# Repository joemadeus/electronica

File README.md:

# led-module
A PCB for a four-LED (plus indicators) light

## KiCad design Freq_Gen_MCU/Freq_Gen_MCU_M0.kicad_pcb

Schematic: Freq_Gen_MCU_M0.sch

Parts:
ADJ_C0, ADJ_C1, ADJ_C2: 100n; C_0805_2012Metric_Pad1.15x1.40mm_HandSolder
ADJ_R0, ADJ_R1, ADJ_R2: 1k; R_0805_2012Metric_Pad1.15x1.40mm_HandSolder
ADJ_SW0, ADJ_SW1, ADJ_SW2: SW_Push; SW_CuK_EP11SD1A
BAT_C1, BAT_C2: 4.7u; C_0805_2012Metric_Pad1.15x1.40mm_HandSolder
BAT_LED1: Conn_01x02; PinHeader_1x02_P1.27mm_Vertical
BAT_R1: 5.1k; R_0805_2012Metric_Pad1.15x1.40mm_HandSolder
BAT_R2: 1k; R_0805_2012Metric_Pad1.15x1.40mm_HandSolder
BAT_U1: MCP73831-2-OT; SOT-23-5
CLK_C1, CLK_C2: 100n; C_0805_2012Metric_Pad1.15x1.40mm_HandSolder
CLK_U1: SI5351A; MSOP-10_3x3mm_P0.5mm
CLK_Y1: Crystal_GND24; Crystal_SMD_3225-4Pin_3.2x2.5mm_HandSoldering
CONN_BAT1: CONN_BAT; JST_PH_S2B-PH-K_1x02_P2.00mm_Horizontal
CONN_USB1: USB; USB_Micro-B_Wuerth_629105150521_CircularHoles
DEBUG_J1: Conn_02x05_Odd_Even; PinHeader_2x05_P1.27mm_Vertical
DEBUG_R1: 1k; R_0805_2012Metric_Pad1.15x1.40mm_HandSolder
HELLO_D1: LED; LED_0805_2012Metric_Pad1.15x1.40mm_HandSolder
HELLO_R1: 6.8; R_0805_2012Metric_Pad1.15x1.40mm_HandSolder
I2C_J1: Conn_01x04; PinHeader_1x04_P1.27mm_Vertical
I2C_R1, I2C_R2: 4.7k; R_0805_2012Metric_Pad1.15x1.40mm_HandSolder
LO_C1, LO_C4: 9.1p; C_0805_2012Metric_Pad1.15x1.40mm_HandSolder
LO_C2, LO_C3: 22p; C_0805_2012Metric_Pad1.15x1.40mm_HandSolder
LO_CONN1: LO; SMA_Jack_Horizontal
LO_L1, LO_L3: 47n; L_0805_2012Metric_Pad1.15x1.40mm_HandSolder
LO_L2: 56n; L_0805_2012Metric_Pad1.15x1.40mm_HandSolder
PWR_C1: 220u; CP_Radial_D6.3mm_P2.50mm
PWR_C2, PWR_C3: 1u; C_0805_2012Metric_Pad1.15x1.40mm_HandSolder
PWR_C4: 10u; C_0805_2012Metric_Pad1.15x1.40mm_HandSolder
PWR_C5: 100n; C_0805_2012Metric_Pad1.15x1.40mm_HandSolder
PWR_CONN1: Conn_01x02; PinHeader_1x02_P1.27mm_Vertical
PWR_D1: D_Schottky; D_SOD-123F
PWR_LED1: Conn_01x02; PinHeader_1x02_P1.27mm_Vertical
PWR_Q1: DMG2301L; SOT-23_Handsoldering
PWR_R1: 10k; R_0805_2012Metric_Pad1.15x1.40mm_HandSolder
PWR_R2: 1k; R_0805_2012Metric_Pad1.15x1.40mm_HandSolder
PWR_U1: AP2112K-3.3; SOT-23-5
PWR_U2: TPD3E001DRLR; SOT-553
U1: ATSAML21E15B-AUT; TQFP-32_7x7mm_P0.8mm
VDDANA_C1: 100n; C_0805_2012Metric_Pad1.15x1.40mm_HandSolder
VDDCORE_C1: 1u; C_0805_2012Metric_Pad1.15x1.40mm_HandSolder
VDDCORE_C2: 100n; C_0805_2012Metric_Pad1.15x1.40mm_HandSolder
VDDIN_C1: 100n; C_0805_2012Metric_Pad1.15x1.40mm_HandSolder

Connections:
/ADJ_0: ADJ_C0.1, ADJ_R0.1, U1.5
/ADJ_1: ADJ_C1.1, ADJ_R1.1, U1.6
/ADJ_2: ADJ_C2.1, ADJ_R2.1, U1.7
/CLK: CLK_U1.10, LO_C1.1, LO_L1.1
/D+: CONN_USB1.3, PWR_U2.2, U1.24
/D-: CONN_USB1.2, PWR_U2.1, U1.23
/GPIO1: DEBUG_J1.6, U1.4
/HELLO: HELLO_R1.2, U1.25
/RESET: DEBUG_J1.10, U1.26
/SCL: CLK_U1.4, I2C_J1.4, I2C_R2.2, U1.18
/SDA: CLK_U1.5, I2C_J1.3, I2C_R1.2, U1.17
/SWCLK: DEBUG_J1.4, DEBUG_R1.2, U1.31
/SWIO: DEBUG_J1.2, U1.32
/VBAT: BAT_C2.1, BAT_U1.3, CONN_BAT1.2, PWR_Q1.3
/VBUS: BAT_C1.1, BAT_LED1.1, BAT_U1.4, PWR_D1.1 (K), PWR_Q1.1
/VDD: CLK_C1.1, CLK_C2.1, CLK_U1.1, CLK_U1.7, DEBUG_J1.1, DEBUG_R1.1, I2C_J1.2, I2C_R1.1, I2C_R2.1, PWR_C3.1, PWR_C4.1, PWR_LED1.1, PWR_U1.5, U1.9, U1.30, VDDANA_C1.1, VDDIN_C1.2
GND: ADJ_C0.2, ADJ_C1.2, ADJ_C2.2, ADJ_SW0.1, ADJ_SW1.1, ADJ_SW2.1, BAT_C1.2, BAT_C2.2, BAT_R1.2, BAT_U1.2, CLK_C1.2, CLK_C2.2, CLK_U1.8, CLK_Y1.2, CLK_Y1.4, CONN_BAT1.1, CONN_USB1.5, DEBUG_J1.3, DEBUG_J1.5, HELLO_D1.1 (K), I2C_J1.1, LO_C1.2, LO_C2.2, LO_C3.2, LO_C4.2, LO_CONN1.2, PWR_C1.2, PWR_C2.2, PWR_C3.2, PWR_C4.2, PWR_C5.2, PWR_R2.2, PWR_U1.2, PWR_U2.3, U1.10, U1.28, VDDANA_C1.2, VDDCORE_C1.1, VDDCORE_C2.1, VDDIN_C1.1
unnamed: ADJ_R0.2, ADJ_SW0.2
unnamed: ADJ_R1.2, ADJ_SW1.2
unnamed: ADJ_R2.2, ADJ_SW2.2
unnamed: BAT_LED1.2, BAT_R2.1
unnamed: BAT_R1.1, BAT_U1.5
unnamed: BAT_R2.2, BAT_U1.1
unnamed: CLK_U1.2, CLK_Y1.1
unnamed: CLK_U1.3, CLK_Y1.3
unnamed: CONN_USB1.1, PWR_C5.1, PWR_D1.2 (A), PWR_U2.5
unnamed: HELLO_D1.2 (A), HELLO_R1.1
unnamed: LO_C2.1, LO_L1.2, LO_L2.1
unnamed: LO_C3.1, LO_L2.2, LO_L3.1
unnamed: LO_C4.1, LO_CONN1.1, LO_L3.2
unnamed: PWR_C1.1, PWR_C2.1, PWR_CONN1.2, PWR_R1.2, PWR_U1.1
unnamed: PWR_CONN1.1, PWR_Q1.2
unnamed: PWR_LED1.2, PWR_R2.1
unnamed: PWR_R1.1, PWR_U1.3
unnamed: U1.27, VDDCORE_C1.2, VDDCORE_C2.2

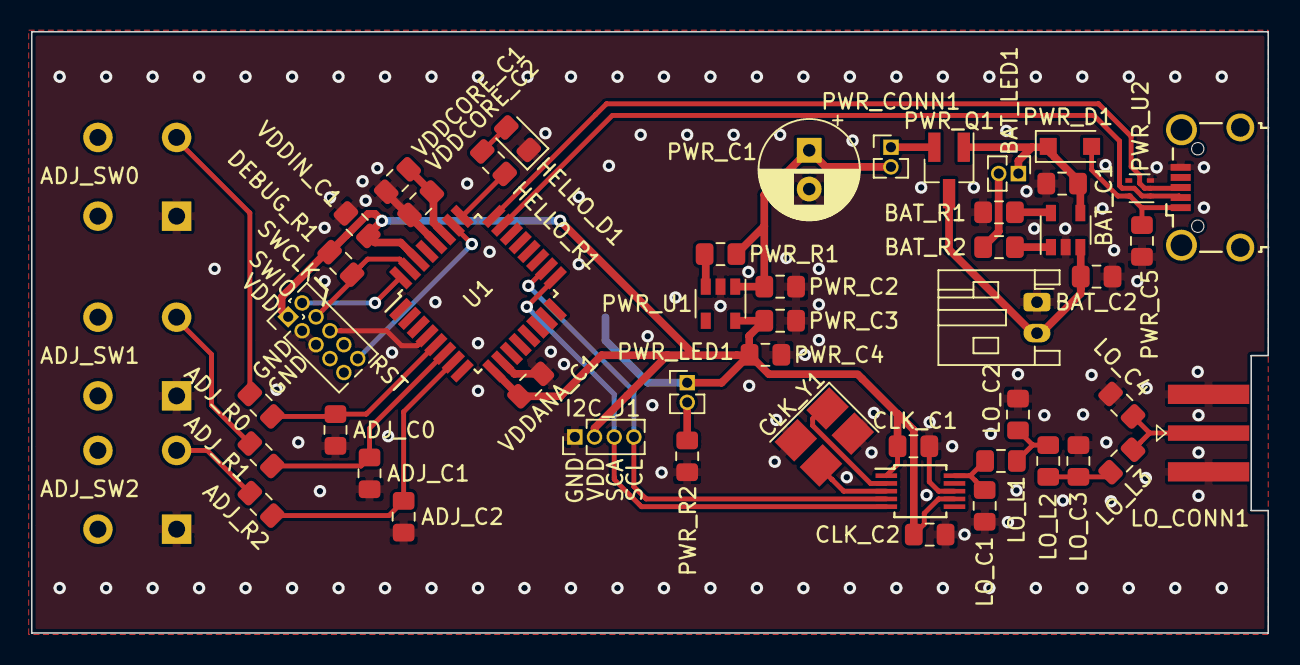
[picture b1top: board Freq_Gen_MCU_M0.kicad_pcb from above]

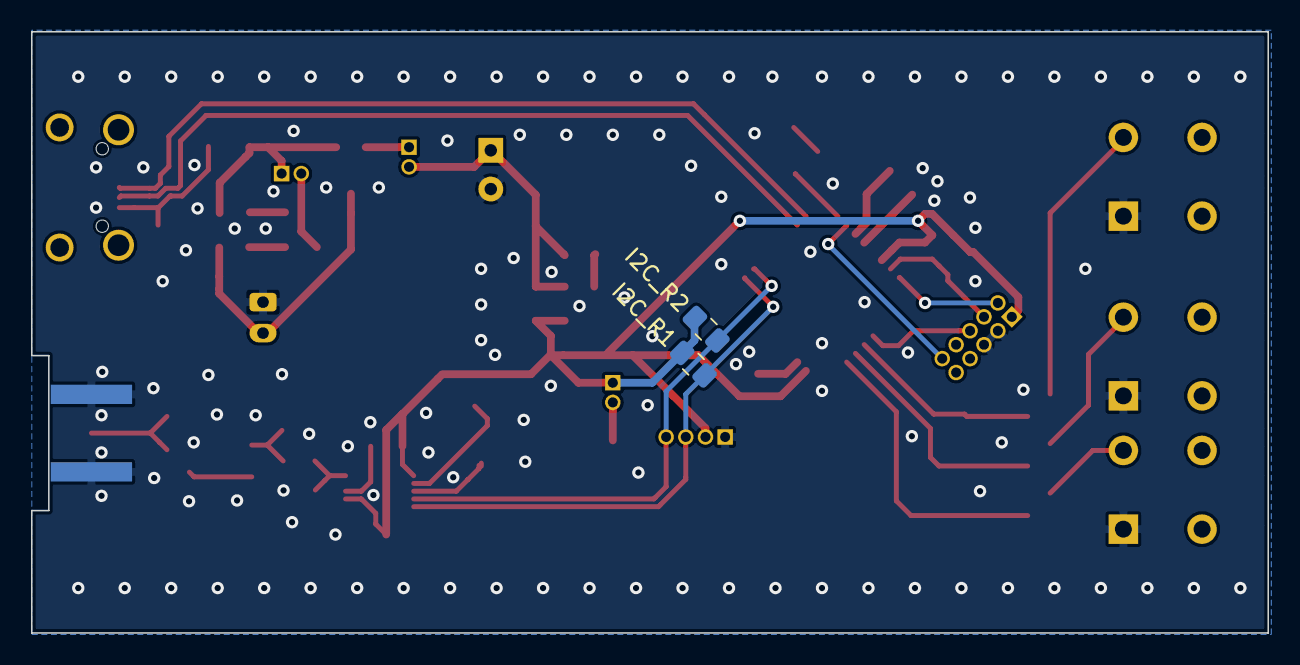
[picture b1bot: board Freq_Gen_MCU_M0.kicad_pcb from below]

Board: 2 copper layers, 79.8 x 38.8 mm, 54 parts (2 on the bottom side), 35 nets.

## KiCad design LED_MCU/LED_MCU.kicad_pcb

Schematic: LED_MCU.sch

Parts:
BAT_C1, BAT_C2: 4.7u; C_0805_2012Metric
BAT_C3: 0.1u; C_0805_2012Metric
BAT_R1: 5k; R_0805_2012Metric
BAT_R2: 1k; R_0805_2012Metric
BAT_U1: LTC2942-1; DFN-6-1EP_3x2mm_P0.5mm_EP1.65x1.35mm
BAT_U2: MCP73831-2-OT; SOT-23-5
C1, C3, C4: 100n; C_0805_2012Metric
C2: 1u; C_0805_2012Metric
CONN_BAT1: CONN_BAT; JST_PH_S2B-PH-K_1x02_P2.00mm_Horizontal
CONN_USB1: USB; USB_Micro-B_Wuerth_629105150521_CircularHoles
H1, H3: MountingHole; MountingHole_2.5mm
H2, H4: MountingHole_Pad; MountingHole_2.7mm_M2.5_DIN965_Pad
HELLO_LED1: HELLO; D_0805_2012Metric_Castellated
HELLO_R1: 6.8; R_1206_3216Metric
IN_C1, IN_C2, IN_C3: 100n; C_0805_2012Metric
IN_J1: Conn_02x03_Odd_Even; PinSocket_2x03_P1.27mm_Vertical
IN_R1, IN_R2, IN_R3: 1k; R_0805_2012Metric
J1: Conn_02x05_Odd_Even; PinHeader_2x05_P1.27mm_Vertical
J2: Conn_02x06_Row_Letter_Last; PinHeader_2x06_P1.27mm_Vertical
J_I2C1: Conn_01x04; PinHeader_1x04_P1.27mm_Vertical
J_RESET1: Conn_01x02; PinHeader_1x02_P1.27mm_Vertical
LED_B1: LED_B; LED_D3.0mm
LED_G1: LED_G; LED_D3.0mm
LED_O1: LED_O; LED_0805_2012Metric_Castellated
LED_R1: LED_R; LED_D3.0mm
LED_W1, LED_W2, LED_W3: LED_W; D_1206_3216Metric_Pad1.42x1.75mm_HandSolder
PWR_C1: 100n; C_0805_2012Metric
PWR_C2: 330uF; CP_Radial_D6.3mm_P2.50mm
PWR_C3, PWR_C5, PWR_C7: 1u; C_0805_2012Metric
PWR_C4: 4.7u; C_0805_2012Metric
PWR_C6: 10u; C_0805_2012Metric
PWR_CONN1: Conn_01x02; PinHeader_1x02_P1.27mm_Vertical
PWR_D1: D_Schottky; D_SOD-123F
PWR_Q1: DMG2301L; SOT-23
PWR_R1: 10k; R_0805_2012Metric
PWR_U1: TPD3E001DRLR; SOT-553
PWR_U2: AP2112K-3.3; SOT-23-5
PWR_U3: LD1117S33TR_SOT223; SOT-223-3_TabPin2
Q1, Q2, Q3: Q_DUAL_NMOS; SO-8_3.9x4.9mm_P1.27mm
R1: 1k; R_0805_2012Metric
R2, R3: 4.7k; R_0805_2012Metric
RB1: 470; R_1206_3216Metric
RB2: 6.8; R_1206_3216Metric
RG1: 470; R_1206_3216Metric
RG2: 10; R_1206_3216Metric
RR1: 470; R_1206_3216Metric
RR2: 10; R_1206_3216Metric
RW1, RW2, RW3: 470; R_1206_3216Metric
RW1-1, RW1-2, RW1-3, RW2-1, RW2-2, RW2-3, RW3-1, RW3-2, RW3-3: 6.8; R_1206_3216Metric
U1: ATSAML21E16B-AUT; TQFP-32_7x7mm_P0.8mm

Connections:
/D+: CONN_USB1.3, PWR_U1.2, U1.24
/D-: CONN_USB1.2, PWR_U1.1, U1.23
/HELLO: HELLO_R1.1, U1.21
/IN1: IN_C1.1, IN_R1.2, U1.11
/IN2: IN_C2.1, IN_R2.2, U1.12
/IN3: IN_C3.1, IN_R3.2, U1.13
/LED_B: RB1.2, U1.3
/LED_G: RG1.2, U1.5
/LED_R: RR1.2, U1.7
/LED_W1: RW1.2, U1.8
/LED_W2: RW2.2, U1.6
/LED_W3: RW3.2, U1.4
/PWR_CC: BAT_U1.5, U1.22
/RESET: J1.10, J_RESET1.1, U1.26
/SCL: BAT_U1.3, J_I2C1.2, R3.2, U1.18
/SDA: BAT_U1.4, J_I2C1.1, R2.2, U1.17
/SWCLK: J1.4, R1.2, U1.31
/SWIO: J1.2, U1.32
/VBAT: BAT_C2.1, BAT_C3.1, BAT_U1.1, BAT_U2.3, PWR_Q1.3
/VBUS: BAT_C1.1, BAT_U2.4, LED_O1.2 (A), PWR_D1.1 (K), PWR_Q1.1
/VCC: PWR_C2.1, PWR_C3.1, PWR_C7.1, PWR_CONN1.1, PWR_R1.2, PWR_U2.1, PWR_U3.3
/VDD: C1.1, C4.2, J1.1, J_I2C1.3, PWR_C5.1, PWR_C6.1, PWR_U2.5, R1.1, R2.1, R3.1, U1.9, U1.30
/V_LED: PWR_C4.1, PWR_U3.2, RB2.1, RG2.1, RR2.1, RW1-1.1, RW1-2.1, RW1-3.1, RW2-1.1, RW2-2.1, RW2-3.1, RW3-1.1, RW3-2.1, RW3-3.1
GND: BAT_C1.2, BAT_C2.2, BAT_C3.2, BAT_R1.2, BAT_U1.2, BAT_U2.2, C1.2, C2.1, C3.1, C4.1, CONN_BAT1.2, CONN_USB1.5, HELLO_LED1.1 (K), IN_C1.2, IN_C2.2, IN_C3.2, IN_J1.2, IN_J1.4, IN_J1.6, J1.3, J1.5, J_I2C1.4, J_RESET1.2, PWR_C1.2, PWR_C2.2, PWR_C3.2, PWR_C4.2, PWR_C5.2, PWR_C6.2, PWR_C7.2, PWR_U1.3, PWR_U2.2, PWR_U3.1, Q1.2, Q1.5, Q2.2, Q2.5, Q3.2, Q3.5, U1.10, U1.28
unnamed: BAT_R1.1, BAT_U2.5
unnamed: BAT_R2.1, LED_O1.1 (K)
unnamed: BAT_R2.2, BAT_U2.1
unnamed: BAT_U1.6, CONN_BAT1.1
unnamed: C2.2, C3.2, U1.27
unnamed: CONN_USB1.1, PWR_C1.1, PWR_D1.2 (A), PWR_U1.5
unnamed: HELLO_LED1.2 (A), HELLO_R1.2
unnamed: IN_J1.1, IN_R1.1
unnamed: IN_J1.3, IN_R2.1
unnamed: IN_J1.5, IN_R3.1
unnamed: J2.1, J2.3, J2.5, Q2.6
unnamed: J2.2, RW2-1.2
unnamed: J2.4, RW2-2.2
unnamed: J2.6, RW2-3.2
unnamed: J2.8, RW3-1.2
unnamed: J2.10, RW3-2.2
unnamed: J2.7, J2.9, J2.11, Q3.6
unnamed: J2.12, RW3-3.2
unnamed: LED_B1.1 (K), Q3.4
unnamed: LED_B1.2 (A), RB2.2
unnamed: LED_G1.1 (K), Q2.4
unnamed: LED_G1.2 (A), RG2.2
unnamed: LED_R1.1 (K), Q1.4
unnamed: LED_R1.2 (A), RR2.2
unnamed: LED_W1.1 (K), LED_W2.1 (K), LED_W3.1 (K), Q1.6
unnamed: LED_W1.2 (A), RW1-1.2
unnamed: LED_W2.2 (A), RW1-2.2
unnamed: LED_W3.2 (A), RW1-3.2
unnamed: PWR_CONN1.2, PWR_Q1.2
unnamed: PWR_R1.1, PWR_U2.3
unnamed: Q1.1, RW1.1
unnamed: Q1.3, RR1.1
unnamed: Q2.1, RW2.1
unnamed: Q2.3, RG1.1
unnamed: Q3.1, RW3.1
unnamed: Q3.3, RB1.1

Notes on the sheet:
RGB
WHITE
BATT CHARGING
BATT MONITORING
90mS 3V3 holdup @1A
USB PWR
BATT SWITCH
μP POWER
LED POWER

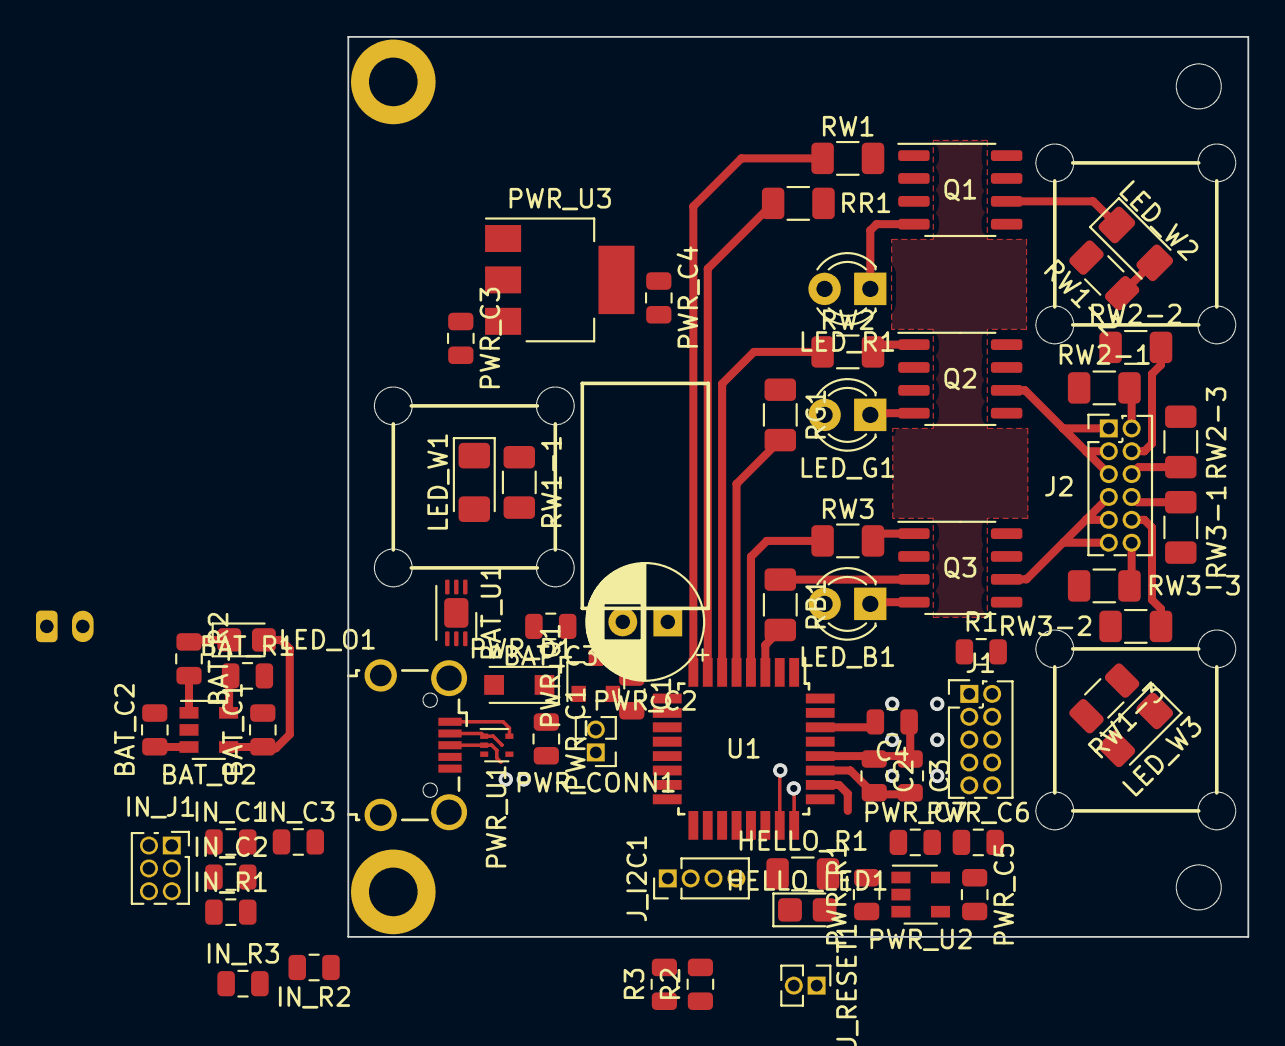
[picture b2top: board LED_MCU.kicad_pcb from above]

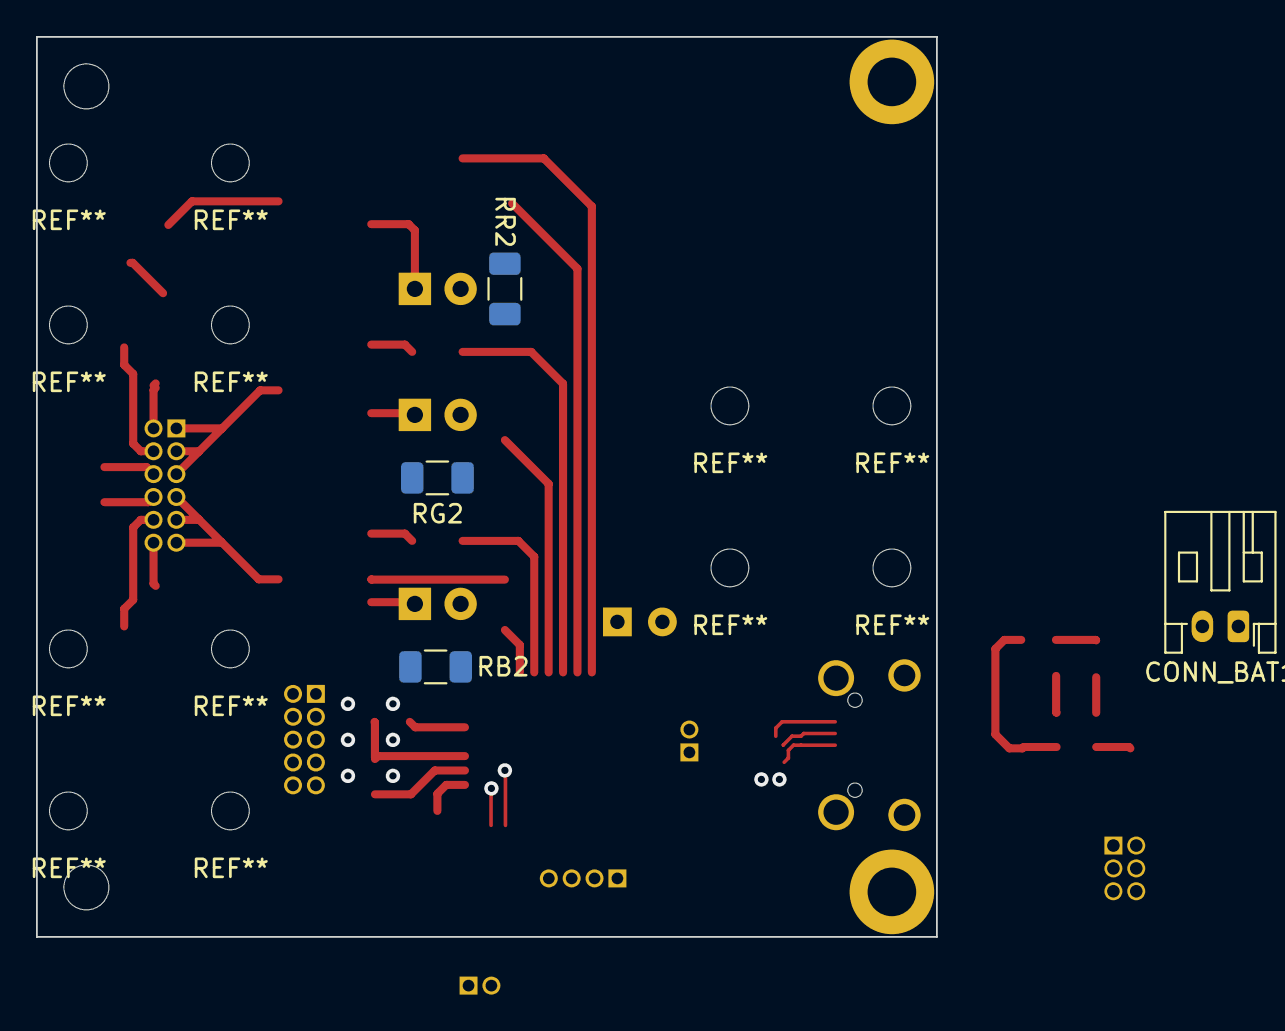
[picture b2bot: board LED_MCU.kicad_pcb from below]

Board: 2 copper layers, 50.0 x 50.0 mm, 76 parts (4 on the bottom side), 60 nets.

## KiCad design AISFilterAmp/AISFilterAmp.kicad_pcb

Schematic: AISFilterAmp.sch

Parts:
J_IN1: Conn_Coaxial; SMA_Jack_Horizontal
J_OUT1: Conn_Coaxial; SMA_Jack_Horizontal
PWR_C1: 4.7u; C_0805_2012Metric_Pad1.15x1.40mm_HandSolder
PWR_C2: 330p; C_0805_2012Metric_Pad1.15x1.40mm_HandSolder
PWR_C3: 10u; C_0805_2012Metric_Pad1.15x1.40mm_HandSolder
PWR_D1: D_Schottky; D_SOD-123F
PWR_J1: Conn_01x02_Female; PinHeader_1x02_P2.54mm_Vertical
PWR_L1: L; L_Taiyo-Yuden_NR-40xx_HandSoldering
PWR_L2: L; L_0805_2012Metric_Pad1.15x1.40mm_HandSolder
PWR_R1: 82.5k; R_0805_2012Metric_Pad1.15x1.40mm_HandSolder
PWR_R2: 13.3k; R_0805_2012Metric_Pad1.15x1.40mm_HandSolder
PWR_R3: 51.1k; R_0805_2012Metric_Pad1.15x1.40mm_HandSolder
RF_C1, RF_C3, RF_C5: 85.53p; C_0805_2012Metric_Pad1.15x1.40mm_HandSolder
RF_C2, RF_C4: 1.744p; C_0805_2012Metric_Pad1.15x1.40mm_HandSolder
RF_C6, RF_C7: C; C_0805_2012Metric_Pad1.15x1.40mm_HandSolder
RF_L1, RF_L3, RF_L5: 11.41n; L_0805_2012Metric_Pad1.15x1.40mm_HandSolder
RF_L2, RF_L4: 559.8n; L_0805_2012Metric_Pad1.15x1.40mm_HandSolder
U1: MSA0505; HP_MSA0505-4_HandSoldering
U2: LM2731XMF; SOT-23-5

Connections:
GND: J_IN1.2, J_OUT1.2, PWR_C1.2, PWR_C3.2, PWR_J1.1, PWR_R2.2, RF_C1.1, RF_C3.1, RF_C5.1, RF_L1.2, RF_L3.2, RF_L5.2, U1.2, U1.4, U2.2
unnamed: J_IN1.1, RF_C1.2, RF_L1.1, RF_L2.1
unnamed: J_OUT1.1, RF_C7.1
unnamed: PWR_C1.1, PWR_J1.2, PWR_L1.1, PWR_R3.2, U2.5
unnamed: PWR_C2.1, PWR_C3.1, PWR_D1.1 (K), PWR_L2.1, PWR_R1.1
unnamed: PWR_C2.2, PWR_R1.2, PWR_R2.1, U2.3
unnamed: PWR_D1.2 (A), PWR_L1.2, U2.1
unnamed: PWR_L2.2, RF_C7.2, U1.3
unnamed: PWR_R3.1, U2.4
unnamed: RF_C2.1, RF_C3.2, RF_L3.1, RF_L4.1
unnamed: RF_C2.2, RF_L2.2
unnamed: RF_C4.1, RF_C5.2, RF_C6.2, RF_L5.1
unnamed: RF_C4.2, RF_L4.2
unnamed: RF_C6.1, U1.1

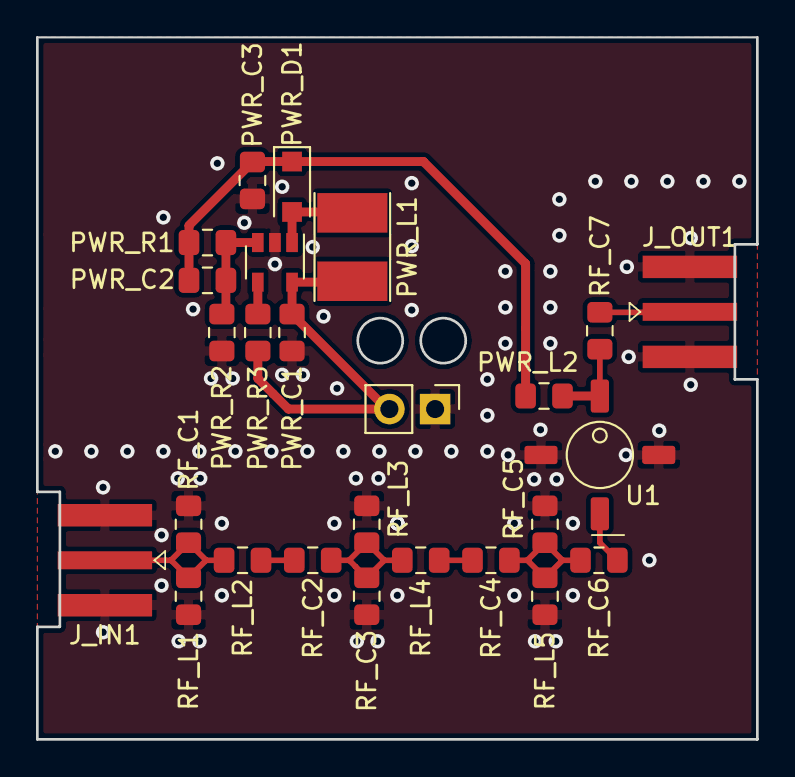
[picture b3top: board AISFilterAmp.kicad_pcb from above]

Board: 2 copper layers, 40.0 x 39.0 mm, 26 parts (0 on the bottom side), 14 nets.

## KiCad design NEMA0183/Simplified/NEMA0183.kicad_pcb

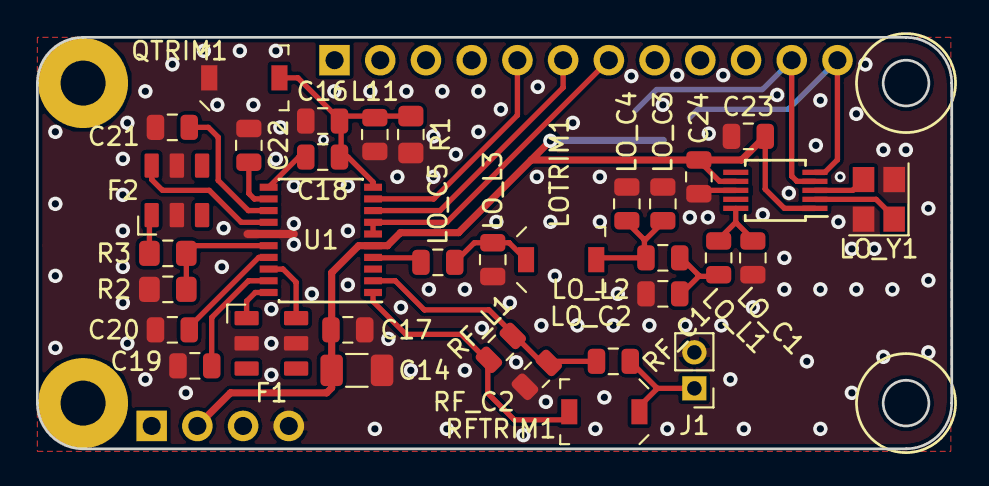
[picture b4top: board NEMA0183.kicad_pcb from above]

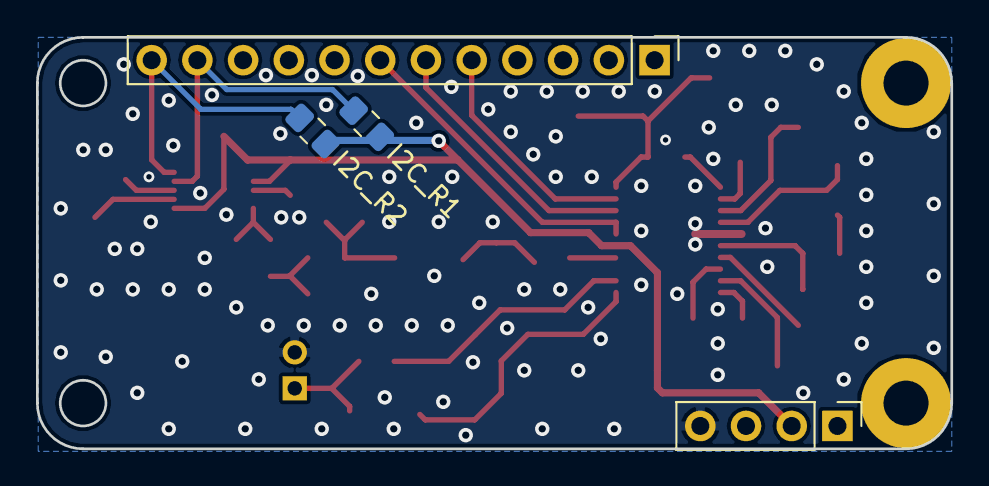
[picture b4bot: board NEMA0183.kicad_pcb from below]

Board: 2 copper layers, 50.8 x 22.9 mm, 38 parts (4 on the bottom side), 28 nets.

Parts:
C14: 22u; C_1206_3216Metric
C16: 30p; C_0805_2012Metric
C17, C23, C24: 100n; C_0805_2012Metric
C18: 4.7p; C_0805_2012Metric
C19, C20, C21, C22: 10n; C_0805_2012Metric
F1, F2: SFECF_10M7; Murata_SFECF-6_HandSoldering
I2C_R1, I2C_R2: 4.7k; R_0805_2012Metric_Pad1.15x1.40mm_HandSolder
J1: RF_IN; PinHeader_1x02_P2.00mm_Vertical
J2: Feather_Top_Female; PinHeader_Adafruit_Feather_Top
J3: Feather_Bottom_Female; PinHeader_1x04_P2.54mm_Vertical
L11: 5.6u; L_0805_2012Metric
LOTRIM1: JZ300; C_Trimmer_Voltronics_JZ
LO_C1, LO_C3: 9.1p; C_0805_2012Metric
LO_C2: 22p; C_0805_2012Metric
LO_C4: 100n; C_0805_2012Metric
LO_C5: 330p; C_0805_2012Metric
LO_L1, LO_L2: 47n; L_0805_2012Metric
LO_L3: 68n; L_0805_2012Metric
LO_U1: SI5351A; MSOP-10_3x3mm_P0.5mm
LO_Y1: Crystal_GND24; Crystal_SMD_3225-4Pin_3.2x2.5mm
QTRIM1: JZ100; C_Trimmer_Voltronics_JZ
R1: 10k; R_0805_2012Metric_Pad1.15x1.40mm_HandSolder
R2, R3: 0; R_0805_2012Metric_Pad1.15x1.40mm_HandSolder
RFTRIM1: JZ300; C_Trimmer_Voltronics_JZ
RF_C1: 82n; C_0805_2012Metric
RF_C2: 330p; C_0805_2012Metric
RF_L1: 68n; L_0805_2012Metric
U1: SA636DK; SSOP-20_4.4x6.5mm_P0.65mm

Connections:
/3V3: C14.1, C17.1, C23.1, C24.2, I2C_R1.1, I2C_R2.2, J3.2, LO_U1.1, LO_U1.7, U1.5
/DAT_OUT: J2.15, U1.9
/LO_IN: LO_C1.1, LO_L1.1, LO_U1.10
/POW_CON_IN: J2.07, U1.8
/RSSI_OUT: J2.11, U1.6, U1.7
/SCL: I2C_R1.2, J2.SCL, LO_U1.4
/SDA: I2C_R2.1, J2.SDA, LO_U1.5
GND: C14.2, C16.2, C17.2, C19.1, C20.1, C21.1, C22.1, C23.2, C24.1, F1.2, F1.5, F2.2, F2.5, J1.2, J3.4, L11.2, LO_C1.2, LO_C2.2, LO_C3.2, LO_C4.2, LO_L3.2, LO_U1.8, LO_Y1.2, LO_Y1.4, QTRIM1.1, R1.2, R2.2, RF_C2.2, U1.15
unnamed: C16.1, C18.2, L11.1, QTRIM1.2, R1.1, U1.10
unnamed: C18.1, U1.11
unnamed: C19.2, U1.19
unnamed: C20.2, U1.17
unnamed: C21.2, U1.13
unnamed: C22.2, U1.12
unnamed: F1.1, U1.20
unnamed: F1.6, U1.18
unnamed: F2.1, R3.2
unnamed: F2.6, U1.14
unnamed: J1.1, RFTRIM1.1, RF_C1.1
unnamed: LOTRIM1.1, LO_C5.1, LO_L3.1
unnamed: LOTRIM1.2, LO_C3.1, LO_C4.1, LO_L2.2
unnamed: LO_C2.1, LO_L1.2, LO_L2.1
unnamed: LO_C5.2, U1.4
unnamed: LO_U1.2, LO_Y1.1
unnamed: LO_U1.3, LO_Y1.3
unnamed: R2.1, R3.1, U1.16
unnamed: RFTRIM1.2, RF_L1.1, U1.1
unnamed: RF_C1.2, RF_C2.1, RF_L1.2, U1.2

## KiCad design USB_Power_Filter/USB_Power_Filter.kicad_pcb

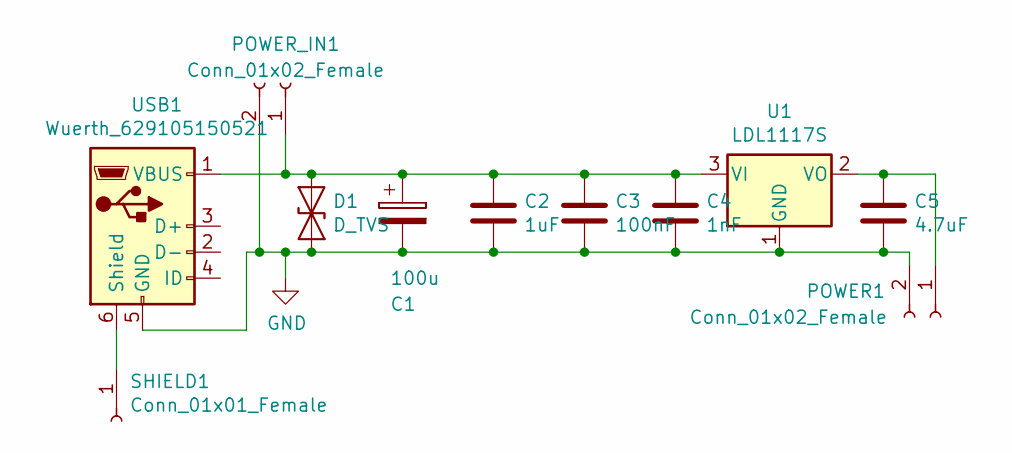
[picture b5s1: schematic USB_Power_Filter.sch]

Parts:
C1: 100u; CP_Radial_D5.0mm_P2.50mm
C2: 1uF; C_0805_2012Metric_Pad1.15x1.40mm_HandSolder
C3: 100nF; C_0805_2012Metric_Pad1.15x1.40mm_HandSolder
C4: 1nF; C_0805_2012Metric_Pad1.15x1.40mm_HandSolder
C5: 4.7uF; C_0805_2012Metric_Pad1.15x1.40mm_HandSolder
D1: D_TVS; D_SOD-323_HandSoldering
POWER1: Conn_01x02_Female; PinHeader_1x02_P2.54mm_Vertical
POWER_IN1: Conn_01x02_Female; PinHeader_1x02_P2.54mm_Vertical
SHIELD1: Conn_01x01_Female; SolderWirePad_1x01_Drill0.8mm
U1: LDL1117S; SOT-223-3_TabPin2
USB1: Wuerth_629105150521; USB_Micro-B_Wuerth_629105150521_CircularHoles

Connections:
GND: C1.2, C2.2, C3.2, C4.2, C5.2, D1.2 (A2), POWER1.2, POWER_IN1.2, U1.1 (GND), USB1.5 (GND)
unnamed: C1.1, C2.1, C3.1, C4.1, D1.1 (A1), POWER_IN1.1, U1.3 (VI), USB1.1 (VBUS)
unnamed: C5.1, POWER1.1, U1.2 (VO)
unnamed: SHIELD1.1, USB1.6 (Shield)

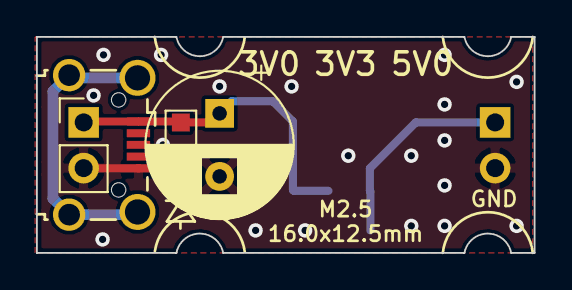
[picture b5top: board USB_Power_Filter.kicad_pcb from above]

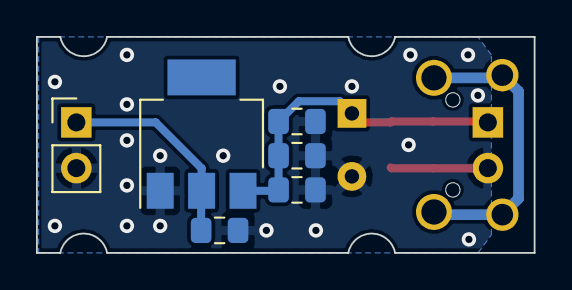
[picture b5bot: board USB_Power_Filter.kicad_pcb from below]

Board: 2 copper layers, 27.7 x 12.0 mm, 10 parts (6 on the bottom side), 3 nets.

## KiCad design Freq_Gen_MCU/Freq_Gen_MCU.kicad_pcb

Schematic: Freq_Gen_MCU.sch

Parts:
ADJ_C1, ADJ_C2, ADJ_C3: 100n; C_0805_2012Metric_Pad1.15x1.40mm_HandSolder
ADJ_R1, ADJ_R2, ADJ_R3: 10k; R_0805_2012Metric_Pad1.15x1.40mm_HandSolder
ADJ_SW1: Rotary_Encoder_Switch; RotaryEncoder_Alps_EC11B-Switch_Horizontal_L20mm
BAT_C1: 10u; C_0805_2012Metric_Pad1.15x1.40mm_HandSolder
BAT_LED1: Conn_01x02; PinHeader_1x02_P1.27mm_Vertical
BAT_R1: 5k; R_0805_2012Metric_Pad1.15x1.40mm_HandSolder
BAT_R2: 1k; R_0805_2012Metric_Pad1.15x1.40mm_HandSolder
BAT_U1: MCP73831-2-OT; SOT-23-5
CLK_C1, CLK_C2: 100n; C_0805_2012Metric_Pad1.15x1.40mm_HandSolder
CLK_U1: SI5351A; MSOP-10_3x3mm_P0.5mm
CLK_Y1: Crystal_GND24; Crystal_SMD_3225-4Pin_3.2x2.5mm_HandSoldering
CONN_BAT1: CONN_BAT; JST_PH_S2B-PH-K_1x02_P2.00mm_Horizontal
CONN_USB1: USB; USB_Micro-B_Wuerth_629105150521_CircularHoles
DEBUG_J1: Conn_02x05_Odd_Even; PinHeader_2x05_P1.27mm_Vertical
D_BUS1: D; D_DO-41_SOD81_P7.62mm_Horizontal
D_TVS1: D_TVS; D_SOD-323_HandSoldering
LO_C1, LO_C4: 15p; C_0805_2012Metric_Pad1.15x1.40mm_HandSolder
LO_C2, LO_C3: 36p; C_0805_2012Metric_Pad1.15x1.40mm_HandSolder
LO_CONN1: LO; SMA_Amphenol_132289_EdgeMount
LO_L1, LO_L3: 68n; L_0805_2012Metric_Pad1.15x1.40mm_HandSolder
LO_L2: 82n; L_0805_2012Metric_Pad1.15x1.40mm_HandSolder
PWR_C1: 220u; CP_Radial_D6.3mm_P2.50mm
PWR_C2, PWR_C3: 1u; C_0805_2012Metric_Pad1.15x1.40mm_HandSolder
PWR_C4: 10u; C_0805_2012Metric_Pad1.15x1.40mm_HandSolder
PWR_CONN1: Conn_01x02; PinHeader_1x02_P1.27mm_Vertical
PWR_LED1: Conn_01x02; PinHeader_1x02_P1.27mm_Vertical
PWR_R1: 0k; R_0805_2012Metric_Pad1.15x1.40mm_HandSolder
PWR_R2: 1k; R_0805_2012Metric_Pad1.15x1.40mm_HandSolder
PWR_U1: AP2112K-3.3; SOT-23-5
R6, R7: 4.7k; R_0805_2012Metric_Pad1.15x1.40mm_HandSolder
RST_C1: 100n; C_0805_2012Metric_Pad1.15x1.40mm_HandSolder
RST_R1: 330; R_0805_2012Metric_Pad1.15x1.40mm_HandSolder
RST_R2: 10k; R_0805_2012Metric_Pad1.15x1.40mm_HandSolder
RST_SW1: SW_Push; SW_PUSH_6mm
U1: BL652; Laird_BL652
VDD_C1: 100n; C_0805_2012Metric_Pad1.15x1.40mm_HandSolder

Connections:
/ADJ_0: ADJ_C1.1, ADJ_R1.1, U1.29
/ADJ_1: ADJ_C2.2, ADJ_R2.1, U1.30
/ADJ_2: ADJ_C3.2, ADJ_R3.2, U1.28
/BAT: U1.23
/CLK: CLK_U1.10, LO_C1.1, LO_L1.1
/RESET: DEBUG_J1.10, RST_C1.1, RST_R1.1, RST_R2.2, U1.7
/SCL: CLK_U1.4, R7.2, U1.37
/SDA: CLK_U1.5, R6.2, U1.36
/SIO_18: DEBUG_J1.6, U1.9
/SWCLK: DEBUG_J1.4, U1.6
/SWIO: DEBUG_J1.2, U1.5
/VBAT: BAT_C1.1, BAT_U1.3, CONN_BAT1.1, D_BUS1.1, PWR_CONN1.1
/VBUS: BAT_LED1.1, BAT_U1.4, CONN_USB1.1, D_BUS1.2, D_TVS1.1
/VDD: CLK_C1.1, CLK_U1.1, DEBUG_J1.1, PWR_C3.1, PWR_C4.1, PWR_LED1.1, PWR_U1.5, R6.1, R7.1, RST_R2.1, U1.26; also elsewhere on the board
GND: ADJ_C1.2, ADJ_C2.1, ADJ_C3.1, ADJ_SW1.C, ADJ_SW1.S2, BAT_C1.2, BAT_R1.2, BAT_U1.2, CLK_C1.2, CLK_C2.1, CLK_U1.8, CLK_Y1.2, CLK_Y1.4, CONN_BAT1.2, CONN_USB1.5, DEBUG_J1.3, DEBUG_J1.5, DEBUG_J1.9, D_TVS1.2, LO_C1.2, LO_C2.2, LO_C3.2, LO_C4.2, LO_CONN1.2, PWR_C1.2, PWR_C2.2, PWR_C3.2, PWR_C4.2, PWR_R2.2, PWR_U1.2, RST_C1.2, RST_SW1.1, U1.1, U1.16, U1.27, U1.39; also elsewhere on the board
unnamed: ADJ_R1.2, ADJ_SW1.B
unnamed: ADJ_R2.2, ADJ_SW1.A
unnamed: ADJ_R3.1, ADJ_SW1.S1
unnamed: BAT_LED1.2, BAT_R2.1
unnamed: BAT_R1.1, BAT_U1.5
unnamed: BAT_R2.2, BAT_U1.1
unnamed: CLK_C2.2, CLK_U1.7
unnamed: CLK_U1.2, CLK_Y1.1
unnamed: CLK_U1.3, CLK_Y1.3
unnamed: LO_C2.1, LO_L1.2, LO_L2.1
unnamed: LO_C3.1, LO_L2.2, LO_L3.1
unnamed: LO_C4.1, LO_CONN1.1, LO_L3.2
unnamed: PWR_C1.1, PWR_C2.1, PWR_CONN1.2, PWR_R1.2, PWR_U1.1
unnamed: PWR_LED1.2, PWR_R2.1
unnamed: PWR_R1.1, PWR_U1.3
unnamed: RST_R1.2, RST_SW1.2

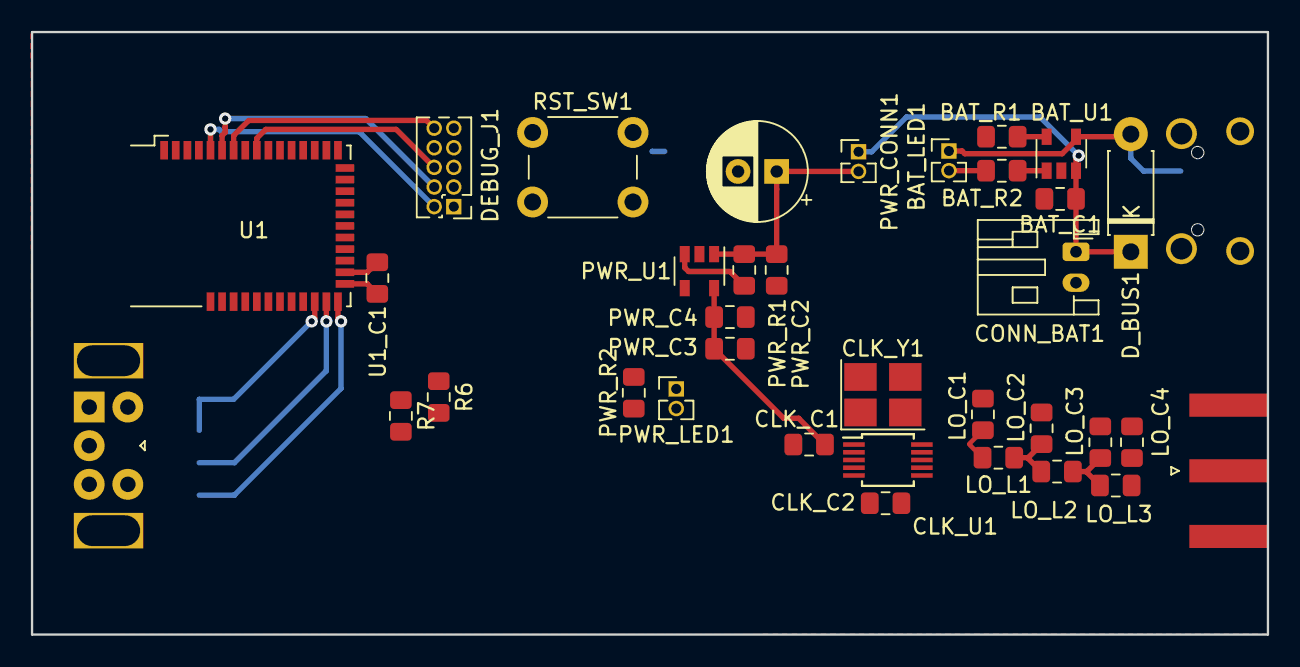
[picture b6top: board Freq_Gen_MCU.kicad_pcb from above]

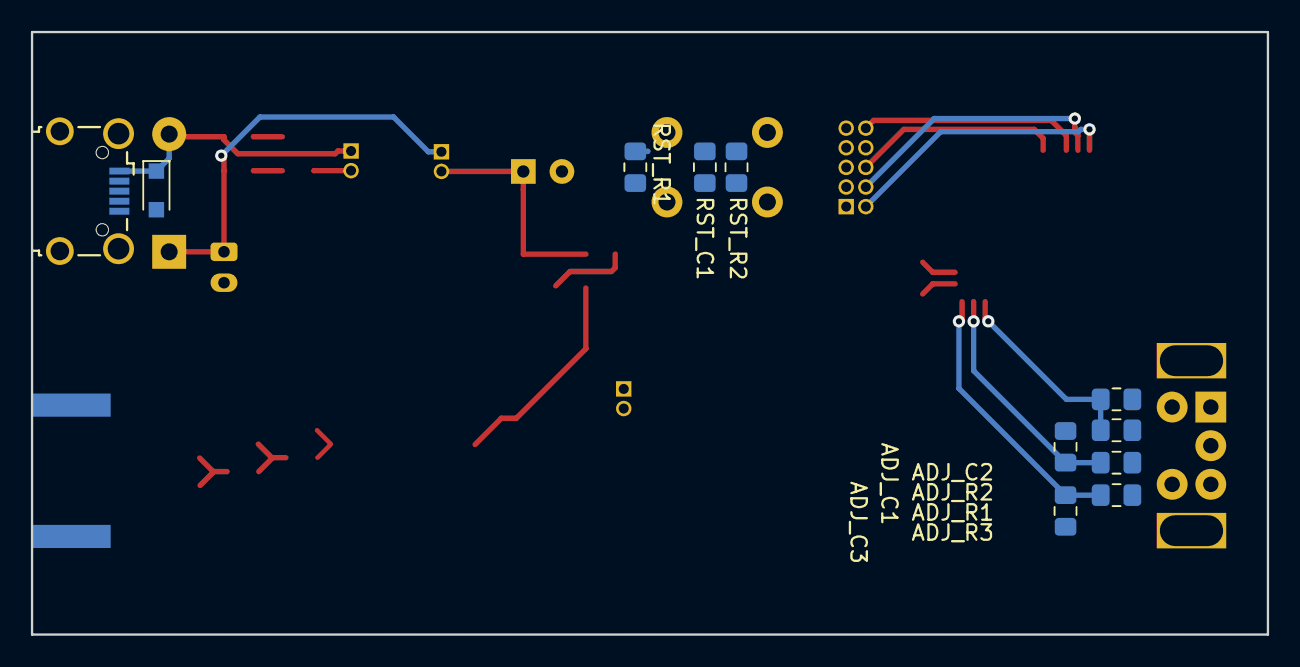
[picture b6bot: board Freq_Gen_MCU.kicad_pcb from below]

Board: 2 copper layers, 80.0 x 39.0 mm, 46 parts (11 on the bottom side), 30 nets.

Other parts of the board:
U1_C1: 100n; C_0805_2012Metric_Pad1.15x1.40mm_HandSolder

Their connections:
/VDD: U1_C1.2; also elsewhere on the board
GND: U1_C1.1; also elsewhere on the board

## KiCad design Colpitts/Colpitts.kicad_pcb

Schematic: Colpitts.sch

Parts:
C1: 1uF; CP_Elec_4x4.5
C2, C3: 33nF; C_1206_HandSoldering
C4: 47nF; C_1206_HandSoldering
C5, C6: 0.1uF; C_1206_HandSoldering
J1: Conn_01x03_Female
L1: 3.3uH; L_1206_HandSoldering
Q1: 2N2222; SOT-223-3_TabPin2
R1: 15k; R_1206_HandSoldering
R2: 5.6k; R_1206_HandSoldering
R3: 68; R_1206_HandSoldering

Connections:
unnamed: C1.1, Q1.1, R1.2, R2.1
unnamed: C1.2, C6.2, J1.2, R2.2, R3.2
unnamed: C2.1, C6.1, J1.1, L1.2, R1.1
unnamed: C2.2, C3.2, C4.2
unnamed: C3.1, C5.2, L1.1, Q1.2
unnamed: C4.1, Q1.3, R3.1
unnamed: C5.1, J1.3

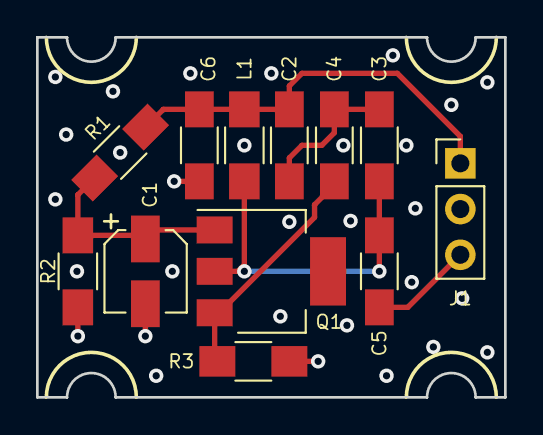
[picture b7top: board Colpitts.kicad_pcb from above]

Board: 2 copper layers, 26.0 x 20.0 mm, 12 parts (0 on the bottom side), 7 nets.

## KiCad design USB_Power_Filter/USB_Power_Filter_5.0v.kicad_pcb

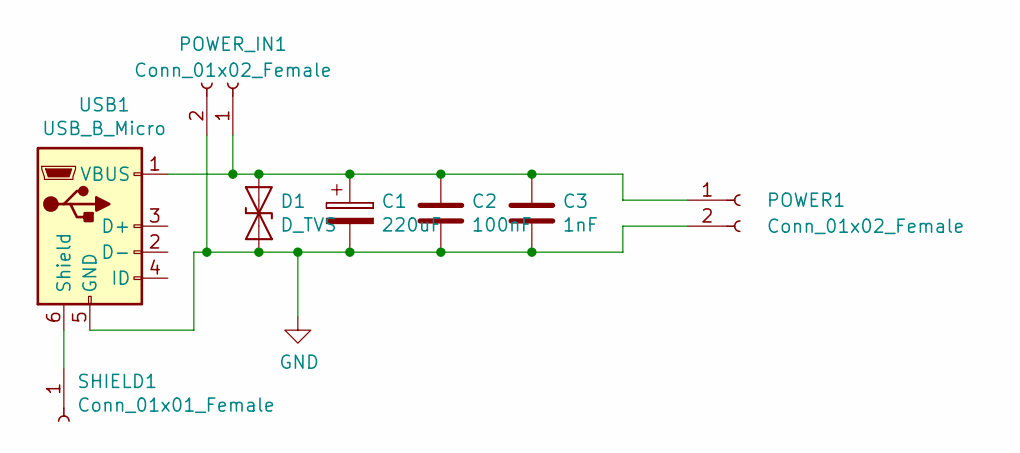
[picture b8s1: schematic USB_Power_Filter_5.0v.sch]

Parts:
C1: 220uF; CP_Elec_6.3x5.8
C2: 100nF; C_1206_HandSoldering
C3: 1nF; C_1206_HandSoldering
D1: D_TVS; D_SMB_Handsoldering
POWER1: Conn_01x02_Female; Pin_Header_Straight_1x02_Pitch2.54mm
POWER_IN1: Conn_01x02_Female; Pin_Header_Straight_1x02_Pitch2.54mm
SHIELD1: Conn_01x01_Female; Pin_Header_Straight_1x01_Pitch2.54mm
USB1: USB_B_Micro; USB_Micro-B_Molex-105017-0001

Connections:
GND: C1.2, C2.2, C3.2, D1.2 (A2), POWER1.2, POWER_IN1.2, USB1.5 (GND)
unnamed: C1.1, C2.1, C3.1, D1.1 (A1), POWER1.1, POWER_IN1.1, USB1.1 (VBUS)
unnamed: SHIELD1.1, USB1.6 (Shield)

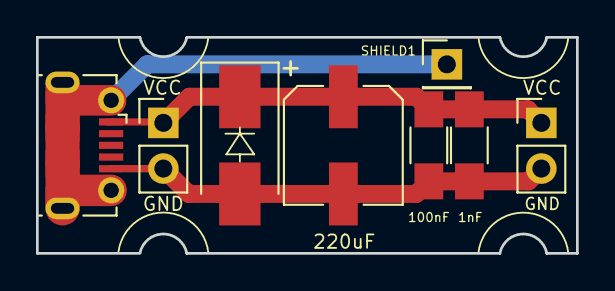
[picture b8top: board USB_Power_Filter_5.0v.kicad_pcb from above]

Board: 2 copper layers, 30.0 x 12.0 mm, 8 parts (0 on the bottom side), 3 nets.

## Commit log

2018-08-06 Adding a design for a USB power filter and regulator
2018-08-06 Adding a Colpitts oscillator
2018-08-06 Adding the design for the LED module/annolight
2018-08-06 Renaming LED module
2018-08-06 Adding some spice models
2018-12-05 Adding NEMA0183
2018-12-18 Adding project LED_MCU, an LED light board with integrated MCU
2019-01-11 More PCB work on AIS Feather receiver
2019-01-11 More PCB work on USB power filter
2019-01-11 Adding a dir for Adafruit-specific KiCAD components
2019-01-11 Adding KiCAD dirs for Maxim and Microchip components
2019-01-11 Adding an AN for SA605
2019-01-11 Much work on the MCU version of the LED module
2019-02-09 Using Si5351 for LO
2019-02-09 Adding filter specs
2019-02-09 Two alternatives for the USB power filter
2019-03-13 As sent to fab
2019-03-13 Adding RF Filters project
2019-06-14 Adding a frequency generator project
2019-06-14 Adding a local gitignore
2019-06-14 Slight mods to USB power filter
2019-06-17 Adding an AIS BP filter and amplifier
2020-03-18 new datasheets
2020-03-18 NEMA0183
2020-03-18 AISFilterAmp
2020-03-18 LED_MCU
2020-03-18 LTSpice_Exp
2020-03-18 RF_Filters
2020-03-18 Freq gen
